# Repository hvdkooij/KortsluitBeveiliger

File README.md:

# KortsluitBeveiliger
DCC Kortsluit Beveiliger

Dit is een ontwerp gemaakt met Kicad 7.0 van het concept op https://www.nproject.org/nl/elektronica/kortsluiting-beperken-met-een-pptc-zekering/

Het staat een ieder vrij om dit voor eigen gebruik toe te passen.
Bij commercieel gebruik neem je ook de verantwoordelijkheid voor ondersteuning op je.

Deze print is getest met PTC waardes tot 0,65 A. Groetere waardes hebben een andere maatvoering van de gaten nodig.

Een waarde van 0,65 A is in de praktijk te groot voor een z21 Start.
Een waarde van 0,4 A kan met sommige combinaties van locomotieven met geluid issues geven.

Voor de Module baan van de VMC (https://www.vmc-epe.nl/) zullen we naar verwachting met 0,4 A of 0,5 A per module gaan werken zodat een kortsluiting op een module niet de hele baan stil legt.

Deze bijdrage is geplaatst door Hugo van der Kooij.

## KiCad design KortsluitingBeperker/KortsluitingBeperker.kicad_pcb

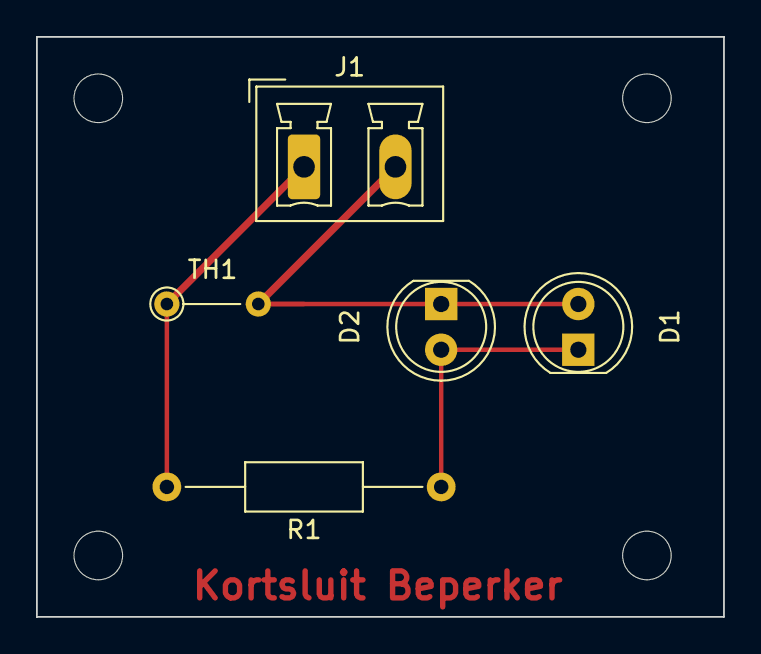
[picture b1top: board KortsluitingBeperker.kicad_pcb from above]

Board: 2 copper layers, 38.2 x 32.2 mm, 9 parts (0 on the bottom side), 3 nets.

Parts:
D1, D2: LED; LED_D5.0mm
J1: Inline; PhoenixContact_MCV_1,5_2-G-5.08_1x02_P5.08mm_Vertical
LB: MountingHole_2.7mm_M2.5
LO: MountingHole_2.7mm_M2.5
R1: 2.2k; R_Axial_DIN0207_L6.3mm_D2.5mm_P15.24mm_Horizontal
RB: MountingHole_2.7mm_M2.5
RO: MountingHole_2.7mm_M2.5
TH1: PTC; R_Axial_DIN0204_L3.6mm_D1.6mm_P5.08mm_Vertical

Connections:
unnamed: D1.2 (A), D2.1 (K), J1.2, TH1.2
unnamed: D1.1 (K), D2.2 (A), R1.1
unnamed: J1.1, R1.2, TH1.1

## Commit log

2024-04-09 Full publish
    Full publish of all files from Kicad
